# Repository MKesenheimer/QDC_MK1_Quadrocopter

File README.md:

QDC MK1 Quadrocopter
====================

Software für einen Miniatur Quadrocopter (Nanocopter) auf Grundlage der MultiWii-Software. Es wird kein Arduino, sondern ein eigenständiger Flightcontroller (AtXmega32A4) verwendet. Die Software, mit der der Quadrocopter kalibriert werden kann, läuft momentan nur unter Mac OS X.

Um die Software zu kompilieren, müssen die Mac OSX Entwicklertools (XCode) oder GNU g++ installiert sein. Außerdem wird avr-gcc und ein Hardware Programmer (z.B. JTAGICE 3) benötigt.

Kompilieren und Hochladen über PDI der Firmware auf den Quadrocopter:
---------------------------------------------------------------------
- cd firmware
- ./make_Wall oder ./make
- make flash

Erzeugen der GUI QuadroCalibration:
-----------------------------------
- QuadroCalibration.xcodeproj mit XCode öffnen
- kompilieren

Sonstiges:
----------
- der Quadrocopter muss über die serielle Schnittstelle USARTD1 mit dem Computer verbunden werden. Dazu bietet sich ein Arduino an, der standardmäßig ein USB-zu-Seriell-Konverter besitzt. Wichtig: Pegel von 3.3V nicht überschreiten!
- an der seriellen Schnittstelle USARTD0 muss der RC-Empfänger angeschlossen werden (nicht im Schaltplan verzeichnet). In dieser Software Version wird ein DSM2 fähiger Deltang rx31b-K1 verwendet.

Der Quadrocopter lässt sich über eine bestimmte Hebelstellung der Fernsteuerung scharfstellen (Motoren an/aus) und neu initialisieren (Selbstkalibrierung von GYRO und ACCELEROMETER). Siehe dazu main.c 

Bekannte Fehler
---------------
- kein Failsafe implementiert
- keine Spannungsüberwachung
- PID-Werte noch nicht optimal

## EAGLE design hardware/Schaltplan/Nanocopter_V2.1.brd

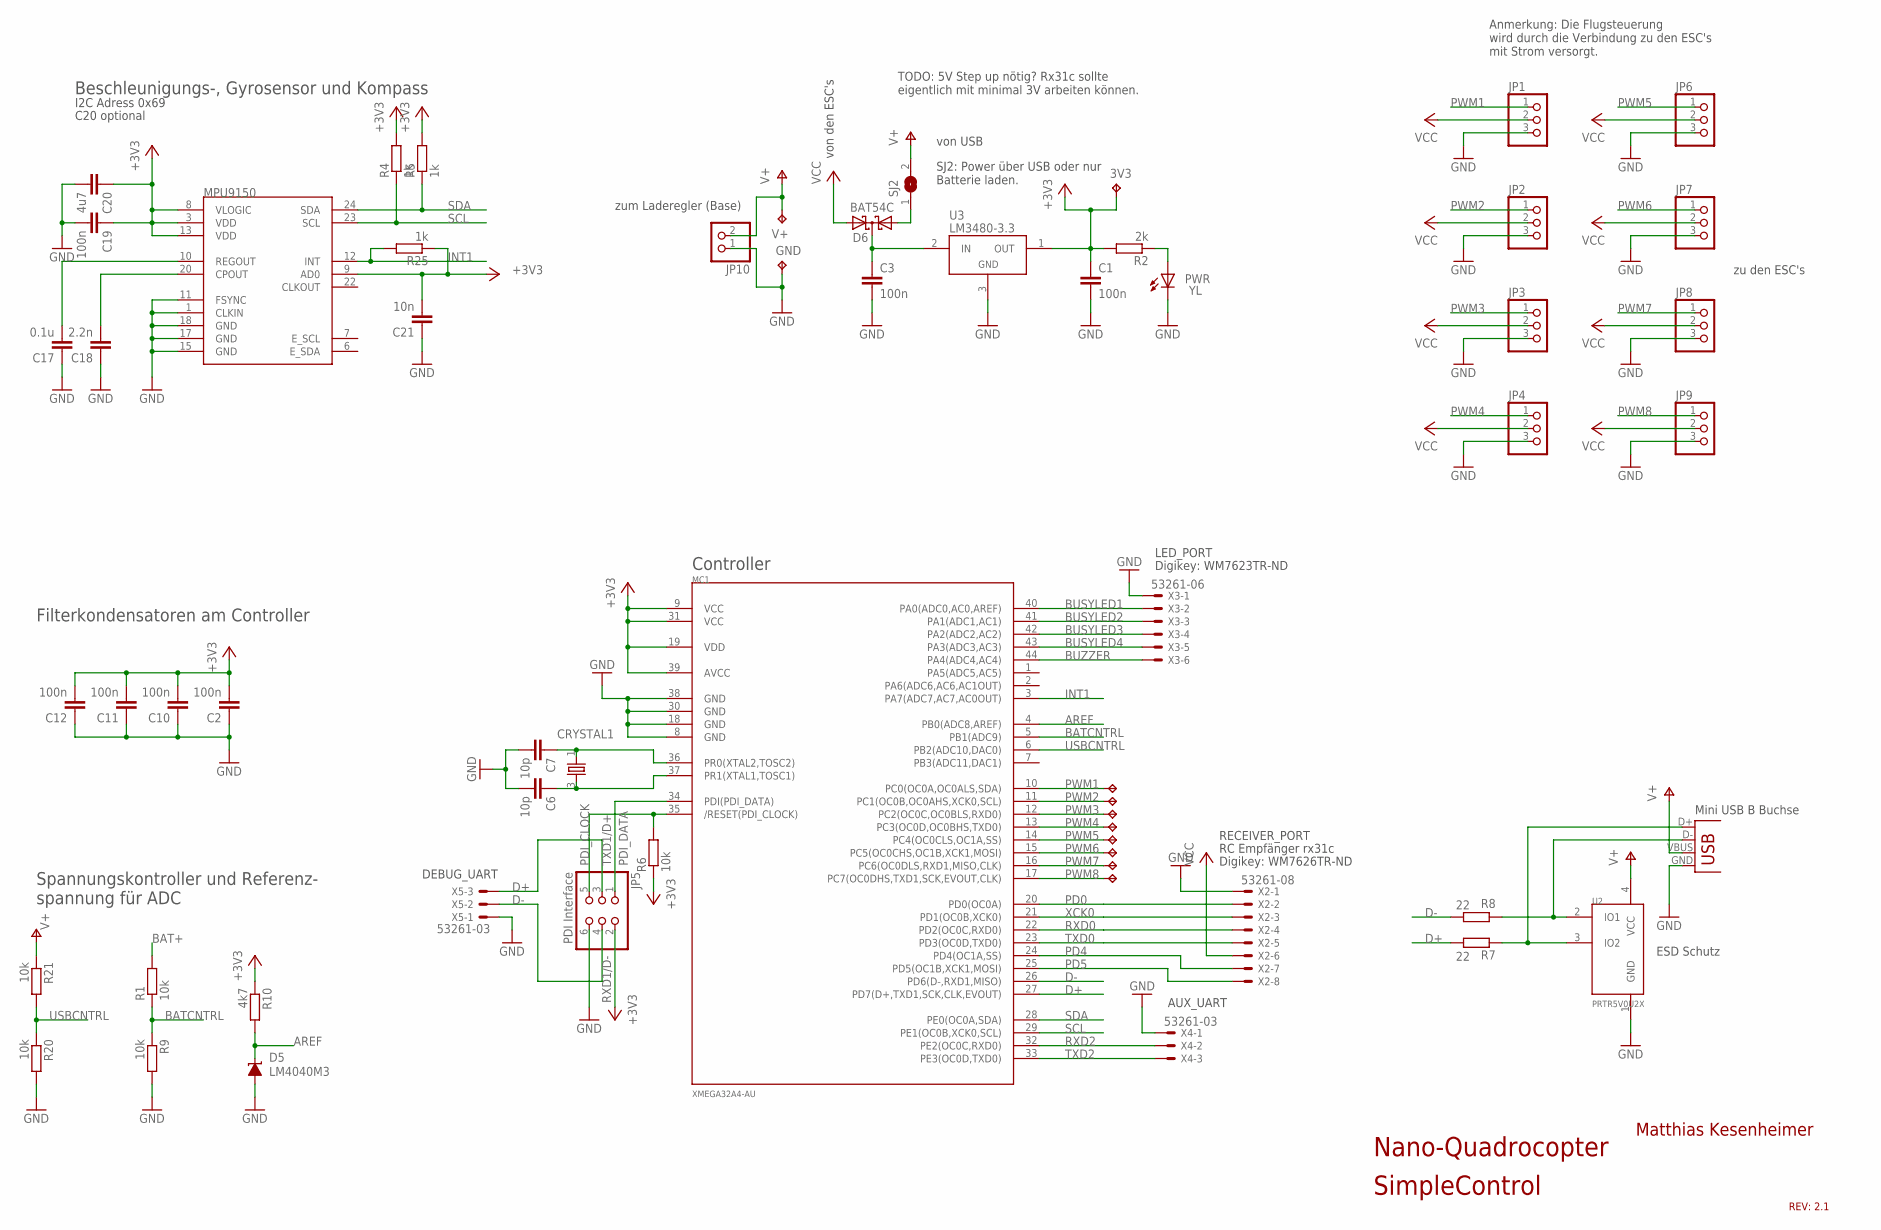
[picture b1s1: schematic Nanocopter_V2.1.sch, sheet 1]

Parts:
3V1, 3V2, 3V3, 3V4, 3V5, 3V6, 3V7, 3V8: TPTP12SQ; TP12SQ
C1, C2, C3, C10, C11, C12, C19: 100n; C0603
C6, C7: 10p; C0603
C17: 0.1u; C0603
C18: 2.2n; C0603
C20: 4u7; C0603
C21: 10n; C0603
CRYSTAL1: CRYSTAL4PIN; CRYSTAL-4PIN
D5: LM4040M3; SOT-23
D6: BAT54C; SOT23
GND: TPTP12SQ; TP12SQ
JP1, JP2, JP3, JP4, JP6, JP7, JP8, JP9: PINHD-1X3; 1X03
JP5: PDI Interface; 2X03
JP10: PINHD-1X2; 1X02
MC1: XMEGA32A4-AU; TQFP44
MPU9150: MPU-9150QFN-24-NP; QFN-24-NP
PWM1: TPTP12SQ; TP12SQ
PWR: YL; CHIPLED_0603
R1, R6, R9, R20, R21: 10k; R0603
R2: 2k; R0603
R4, R5, R25: 1k; R0603
R7, R8: 22; R0603
R10: 4k7; R0603
SJ2: SJ
U2: PRTR5V0U2X; SOT143B
U3: LM3480-3.3; SOT-23-3
V+: TPTP12SQ; TP12SQ
X1: USBSMD; USB-MINIB
X2: 53261-08
X3: 53261-06
X4, X5: 53261-03

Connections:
+3V3: 3V3.TP, C1.1, C2.2, C10.2, C11.2, C12.2, C19.1, C20.1, C21.2, JP5.2, MC1.9 (VCC), MC1.19 (VDD), MC1.31 (VCC), MC1.39 (AVCC), MPU9150.3 (VDD), MPU9150.8 (VLOGIC), MPU9150.9 (AD0), MPU9150.13 (VDD), R2.2, R4.2, R5.2, R6.1, R10.1, R25.1, U3.1 (OUT)
AREF: D5.1 (C), MC1.4 (PB0(ADC8,AREF)), R10.2
BAT+: R1.2
BATCNTRL: MC1.5 (PB1(ADC9)), R1.1, R9.1
BUSYLED1: MC1.40 (PA0(ADC0,AC0,AREF)), X3.2
BUSYLED2: MC1.41 (PA1(ADC1,AC1)), X3.3
BUSYLED3: MC1.42 (PA2(ADC2,AC2)), X3.4
BUSYLED4: MC1.43 (PA3(ADC3,AC3)), X3.5
BUZZER: MC1.44 (PA4(ADC4,AC4)), X3.6
D+: JP5.3, MC1.27 (PD7(D+,TXD1,SCK,CLK,EVOUT)), R7.2, X5.3
D-: JP5.4, MC1.26 (PD6(D-,RXD1,MISO)), R8.2, X5.2
GND: C1.2, C2.1, C3.2, C6.2, C7.2, C10.1, C11.1, C12.1, C17.1, C18.1, C19.2, C20.2, C21.1, D5.2 (A), GND.TP, JP1.3, JP2.3, JP3.3, JP4.3, JP5.6, JP6.3, JP7.3, JP8.3, JP9.3, JP10.1, MC1.8 (GND), MC1.18 (GND), MC1.30 (GND), MC1.38 (GND), MPU9150.1 (CLKIN), MPU9150.11 (FSYNC), MPU9150.15 (GND), MPU9150.17 (GND), MPU9150.18 (GND), PWR.C, R9.2, R20.2, U2.1 (GND), U3.3 (GND), X1.GND, X2.1, X3.1, X4.1, X5.1; also elsewhere on the board
INT1: MC1.3 (PA7(ADC7,AC7,AC0OUT)), MPU9150.12 (INT), R25.2
unnamed: C18.2, MPU9150.20 (CPOUT)
unnamed: C17.2, MPU9150.10 (REGOUT)
unnamed: C3.1, D6.3 (CC), U3.2 (IN)
unnamed: PWR.A, R2.1
unnamed: C7.1, CRYSTAL1.1, MC1.36 (PR0(XTAL2,TOSC2))
unnamed: C6.1, CRYSTAL1.3 (2), MC1.37 (PR1(XTAL1,TOSC1))
unnamed: D6.1 (A1), SJ2.1
PD0: MC1.20 (PD0(OC0A)), X2.2
PD4: MC1.24 (PD4(OC1A,SS)), X2.7
PD5: MC1.25 (PD5(OC1B,XCK1,MOSI)), X2.8
PDI_CLOCK: JP5.5, MC1.35 (/RESET(PDI_CLOCK)), R6.2
PDI_DATA: JP5.1, MC1.34 (PDI(PDI_DATA))
PWM1: JP1.1, MC1.10 (PC0(OC0A,OC0ALS,SDA)), PWM1.TP
PWM2: 3V2.TP, JP2.1, MC1.11 (PC1(OC0B,OC0AHS,XCK0,SCL))
PWM3: 3V4.TP, JP3.1, MC1.12 (PC2(OC0C,OC0BLS,RXD0))
PWM4: 3V5.TP, JP4.1, MC1.13 (PC3(OC0D,OC0BHS,TXD0))
PWM5: 3V1.TP, JP6.1, MC1.14 (PC4(OC0CLS,OC1A,SS))
PWM6: 3V6.TP, JP7.1, MC1.15 (PC5(OC0CHS,OC1B,XCK1,MOSI))
PWM7: 3V7.TP, JP8.1, MC1.16 (PC6(OC0DLS,RXD1,MISO,CLK))
PWM8: 3V8.TP, JP9.1, MC1.17 (PC7(OC0DHS,TXD1,SCK,EVOUT,CLK))
RXD0: MC1.22 (PD2(OC0C,RXD0)), X2.4
RXD2: MC1.32 (PE2(OC0C,RXD0)), X4.2
SCL: MC1.29 (PE1(OC0B,XCK0,SCL)), MPU9150.23 (SCL), R4.1
SDA: MC1.28 (PE0(OC0A,SDA)), MPU9150.24 (SDA), R5.1
TXD0: MC1.23 (PD3(OC0D,TXD0)), X2.5
TXD2: MC1.33 (PE3(OC0D,TXD0)), X4.3
USB+: R7.1, U2.3 (IO2), X1.D+
USB-: R8.1, U2.2 (IO1), X1.D-
USBCNTRL: MC1.6 (PB2(ADC10,DAC0)), R20.1, R21.2
V+: JP10.2, R21.1, SJ2.2, U2.4 (VCC), V+.TP, X1.VBUS
VCC: D6.2 (A2), JP1.2, JP2.2, JP3.2, JP4.2, JP6.2, JP7.2, JP8.2, JP9.2, X2.6; also elsewhere on the board
XCK0: MC1.21 (PD1(OC0B,XCK0)), X2.3

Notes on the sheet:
I2C Adress 0x69
Beschleunigungs-, Gyrosensor und Kompass
Matthias Kesenheimer
REV: 2.1
Nano-Quadrocopter
SimpleControl
Mini USB B Buchse
Controller
Filterkondensatoren am Controller
C20 optional
Spannungskontroller und Referenz- spannung für ADC
ESD Schutz
RC Empfänger rx31c
Digikey: WM7626TR-ND
Digikey: WM7623TR-ND
RXD1/D-
TXD1/D+
DEBUG_UART
AUX_UART
LED_PORT
RECEIVER_PORT
zum Laderegler (Base)
zu den ESC's
Anmerkung: Die Flugsteuerung wird durch die Verbindung zu den ESC's mit Strom versorgt.
von den ESC's
von USB
SJ2: Power über USB oder nur Batterie laden.
TODO: 5V Step up nötig? Rx31c sollte eigentlich mit minimal 3V arbeiten können.

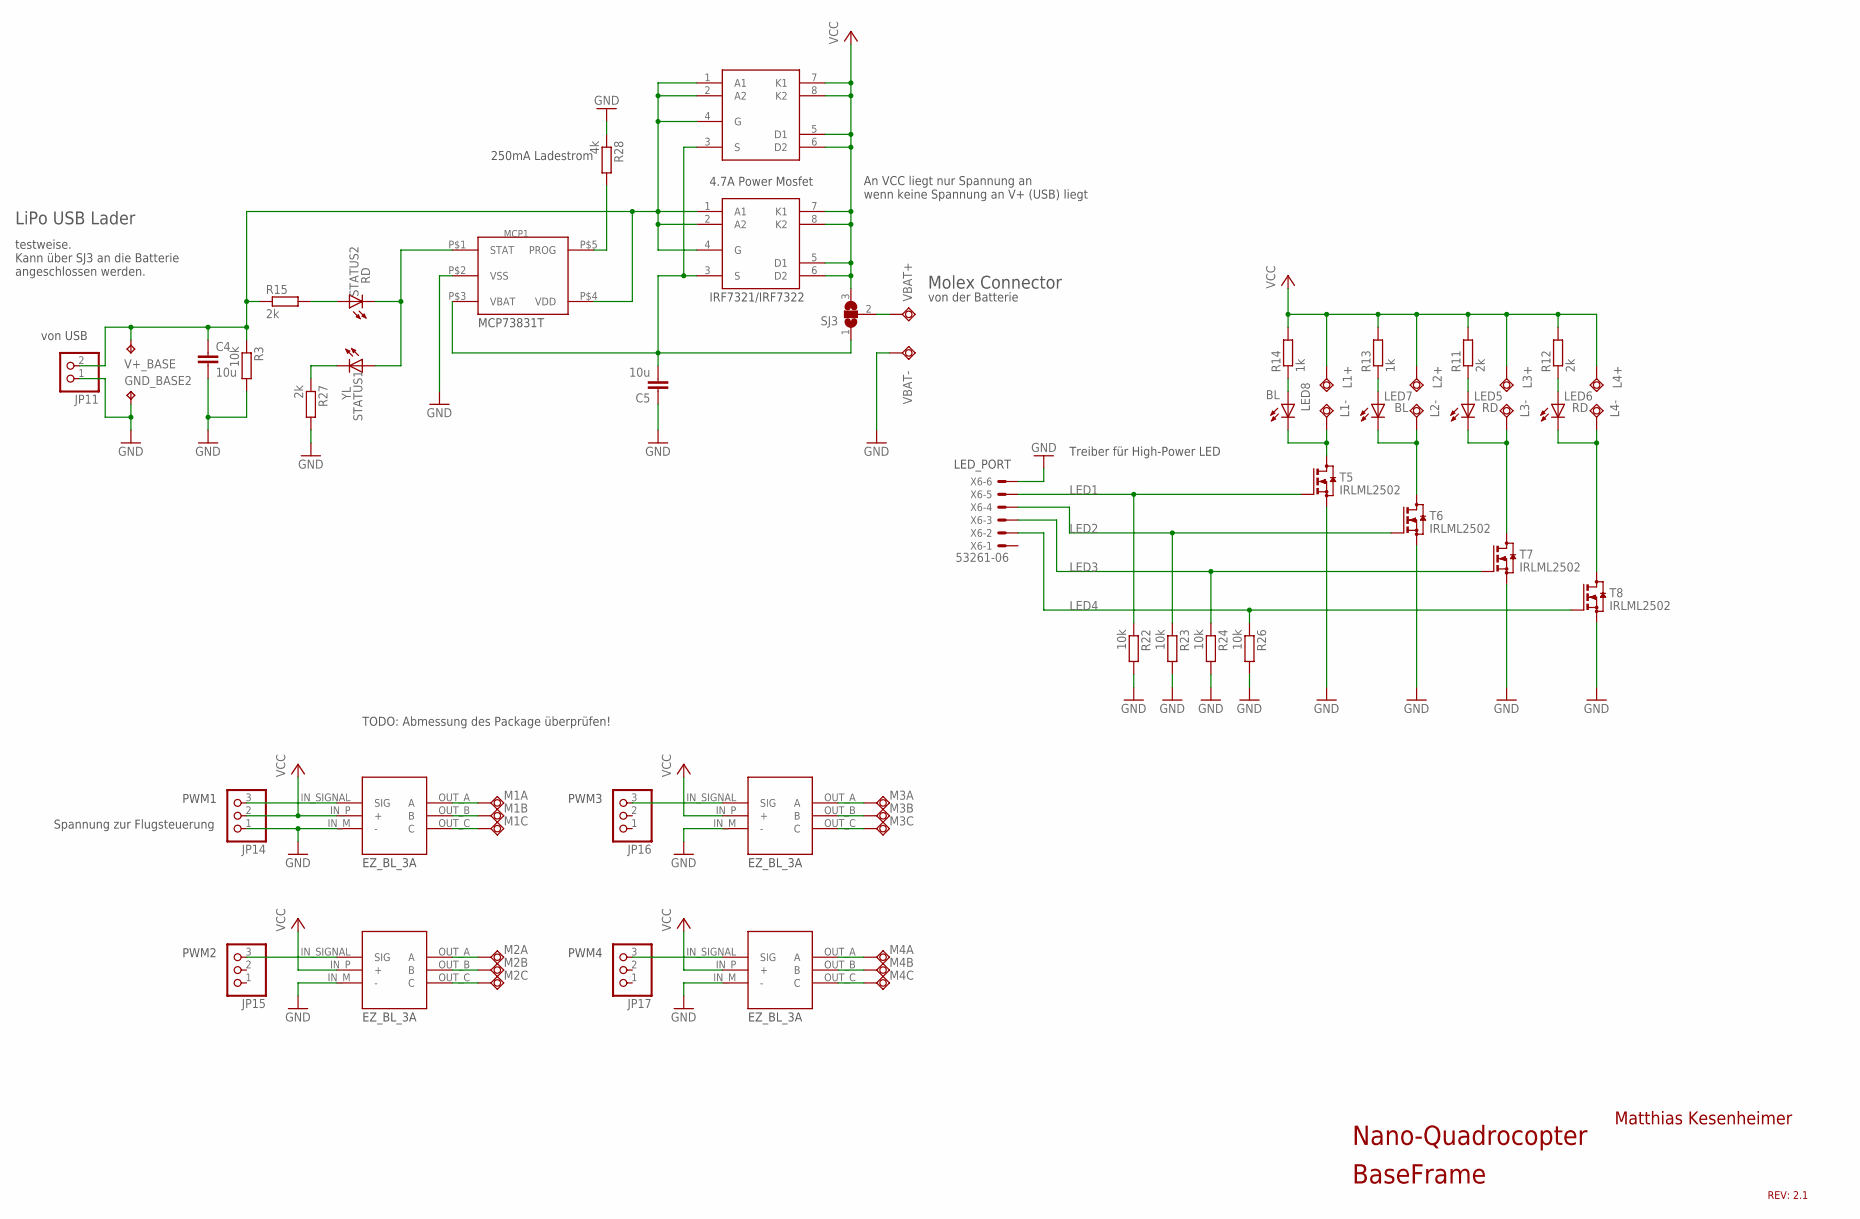
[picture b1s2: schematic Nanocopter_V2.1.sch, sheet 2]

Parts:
C4, C5: 10u; C1206
GND_BASE2: TPTP12SQ; TP12SQ
JP11: PINHD-1X2/90; 1X02/90
JP14, JP15, JP16, JP17: PINHD-1X3/90; 1X03/90
L1+, L1-, L2+, L2-, L3+, L3-, L4+, L4-: TPSQTP20SQ; TP20SQ
LED5, LED6: RD; CHIPLED_0603
LED7, LED8: BL; CHIPLED_0603
M1A, M1B, M1C, M2A, M2B, M2C, M3A, M3B, M3C, M4A, M4B, M4C: TPSQTP20SQ; TP20SQ
MCP1: MCP73831; 5PIN_SOT23
R3, R22, R23, R24, R26: 10k; R0603
R11, R12, R15, R27: 2k; R0603
R13, R14: 1k; R0603
R28: 4k; R0603
SJ3: SJ2W; SJ_2
STATUS1: YL; CHIPLED_0603
STATUS2: RD; CHIPLED_0603
T5, T6, T7, T8: IRLML2502; SOT23
U$1, U$2, U$3, U$4: EAZY_BL_3A; EZ_BL_3A_P
U$5, U$6: IRF7321; SO8
V+_BASE: TPTP12SQ; TP12SQ
VBAT+: TPSQTP20SQ; TP20SQ
VBAT-: TPSQTP20SQ; TP20SQ
X6: 53261-06

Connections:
GND: C4.2, C5.1, GND_BASE2.TP, JP11.1, JP14.1, MCP1.P$2 (VSS), R3.2, R22.2, R23.2, R24.2, R26.2, R27.2, R28.1, T5.2 (S), T6.2 (S), T7.2 (S), T8.2 (S), U$1.IN_M (-), U$2.IN_M (-), U$3.IN_M (-), U$4.IN_M (-), VBAT-.TP, X6.6; also elsewhere on the board
LED1: R22.1, T5.1 (G), X6.5
LED2: R23.1, T6.1 (G), X6.4
LED3: R24.1, T7.1 (G), X6.3
LED4: R26.1, T8.1 (G), X6.2
unnamed: LED5.A, R11.1
unnamed: LED6.A, R12.1
unnamed: LED7.A, R13.1
unnamed: L1-.TP, LED8.C, T5.3 (D)
unnamed: L3-.TP, LED5.C, T7.3 (D)
unnamed: L4-.TP, LED6.C, T8.3 (D)
unnamed: L2-.TP, LED7.C, T6.3 (D)
unnamed: MCP1.P$5 (PROG), R28.2
unnamed: JP14.3, U$1.IN_SIGNAL (SIG)
unnamed: M2A.TP, U$2.OUT_A (A)
unnamed: LED8.A, R14.1
unnamed: C5.2, MCP1.P$3 (VBAT), SJ3.1, U$5.3 (S), U$6.3 (S)
unnamed: M2B.TP, U$2.OUT_B (B)
unnamed: M2C.TP, U$2.OUT_C (C)
unnamed: R15.2, STATUS2.A
unnamed: M1A.TP, U$1.OUT_A (A)
unnamed: M1B.TP, U$1.OUT_B (B)
unnamed: M1C.TP, U$1.OUT_C (C)
unnamed: JP15.3, U$2.IN_SIGNAL (SIG)
unnamed: M3A.TP, U$3.OUT_A (A)
unnamed: M3B.TP, U$3.OUT_B (B)
unnamed: M3C.TP, U$3.OUT_C (C)
unnamed: JP16.3, U$3.IN_SIGNAL (SIG)
unnamed: M4A.TP, U$4.OUT_A (A)
unnamed: M4B.TP, U$4.OUT_B (B)
unnamed: M4C.TP, U$4.OUT_C (C)
unnamed: JP17.3, U$4.IN_SIGNAL (SIG)
unnamed: R27.1, STATUS1.C
unnamed: MCP1.P$1 (STAT), STATUS1.A, STATUS2.C
unnamed: SJ3.2, VBAT+.TP
VCC: JP14.2, L1+.TP, L2+.TP, L3+.TP, L4+.TP, R11.2, R12.2, R13.2, R14.2, SJ3.3, U$1.IN_P (+), U$2.IN_P (+), U$3.IN_P (+), U$4.IN_P (+), U$5.5 (D1), U$5.6 (D2), U$5.7 (K1), U$5.8 (K2), U$6.5 (D1), U$6.6 (D2), U$6.7 (K1), U$6.8 (K2); also elsewhere on the board
VDD: C4.1, JP11.2, MCP1.P$4 (VDD), R3.1, R15.1, U$5.1 (A1), U$5.2 (A2), U$5.4 (G), U$6.1 (A1), U$6.2 (A2), U$6.4 (G), V+_BASE.TP

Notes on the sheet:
LiPo USB Lader
250mA Ladestrom
Matthias Kesenheimer
REV: 2.1
Nano-Quadrocopter
BaseFrame
Treiber für High-Power LED
Molex Connector
PWM1
PWM2
PWM3
PWM4
Spannung zur Flugsteuerung
von der Batterie
von USB
LED_PORT
testweise. Kann über SJ3 an die Batterie angeschlossen werden.
4.7A Power Mosfet
IRF7321/IRF7322
MCP73831T
An VCC liegt nur Spannung an wenn keine Spannung an V+ (USB) liegt
TODO: Abmessung des Package überprüfen!
EZ_BL_3A

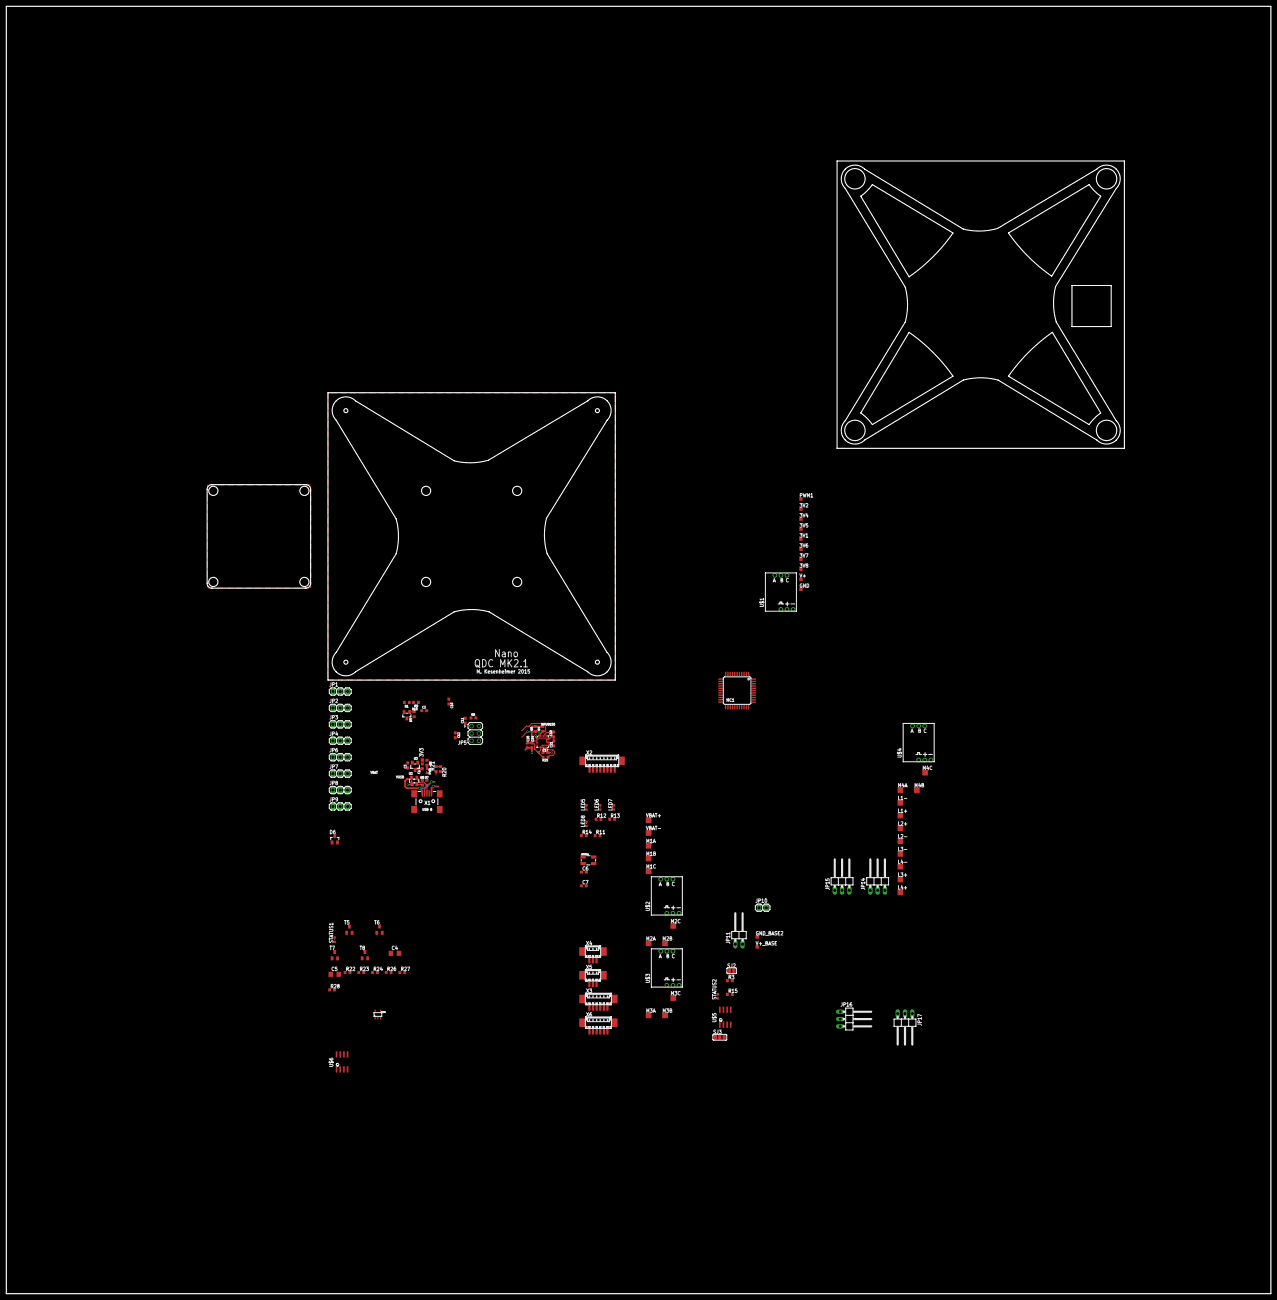
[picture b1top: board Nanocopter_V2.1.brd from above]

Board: 2 copper layers, 440.1 x 448.0 mm, 122 parts (0 on the bottom side), 79 nets.

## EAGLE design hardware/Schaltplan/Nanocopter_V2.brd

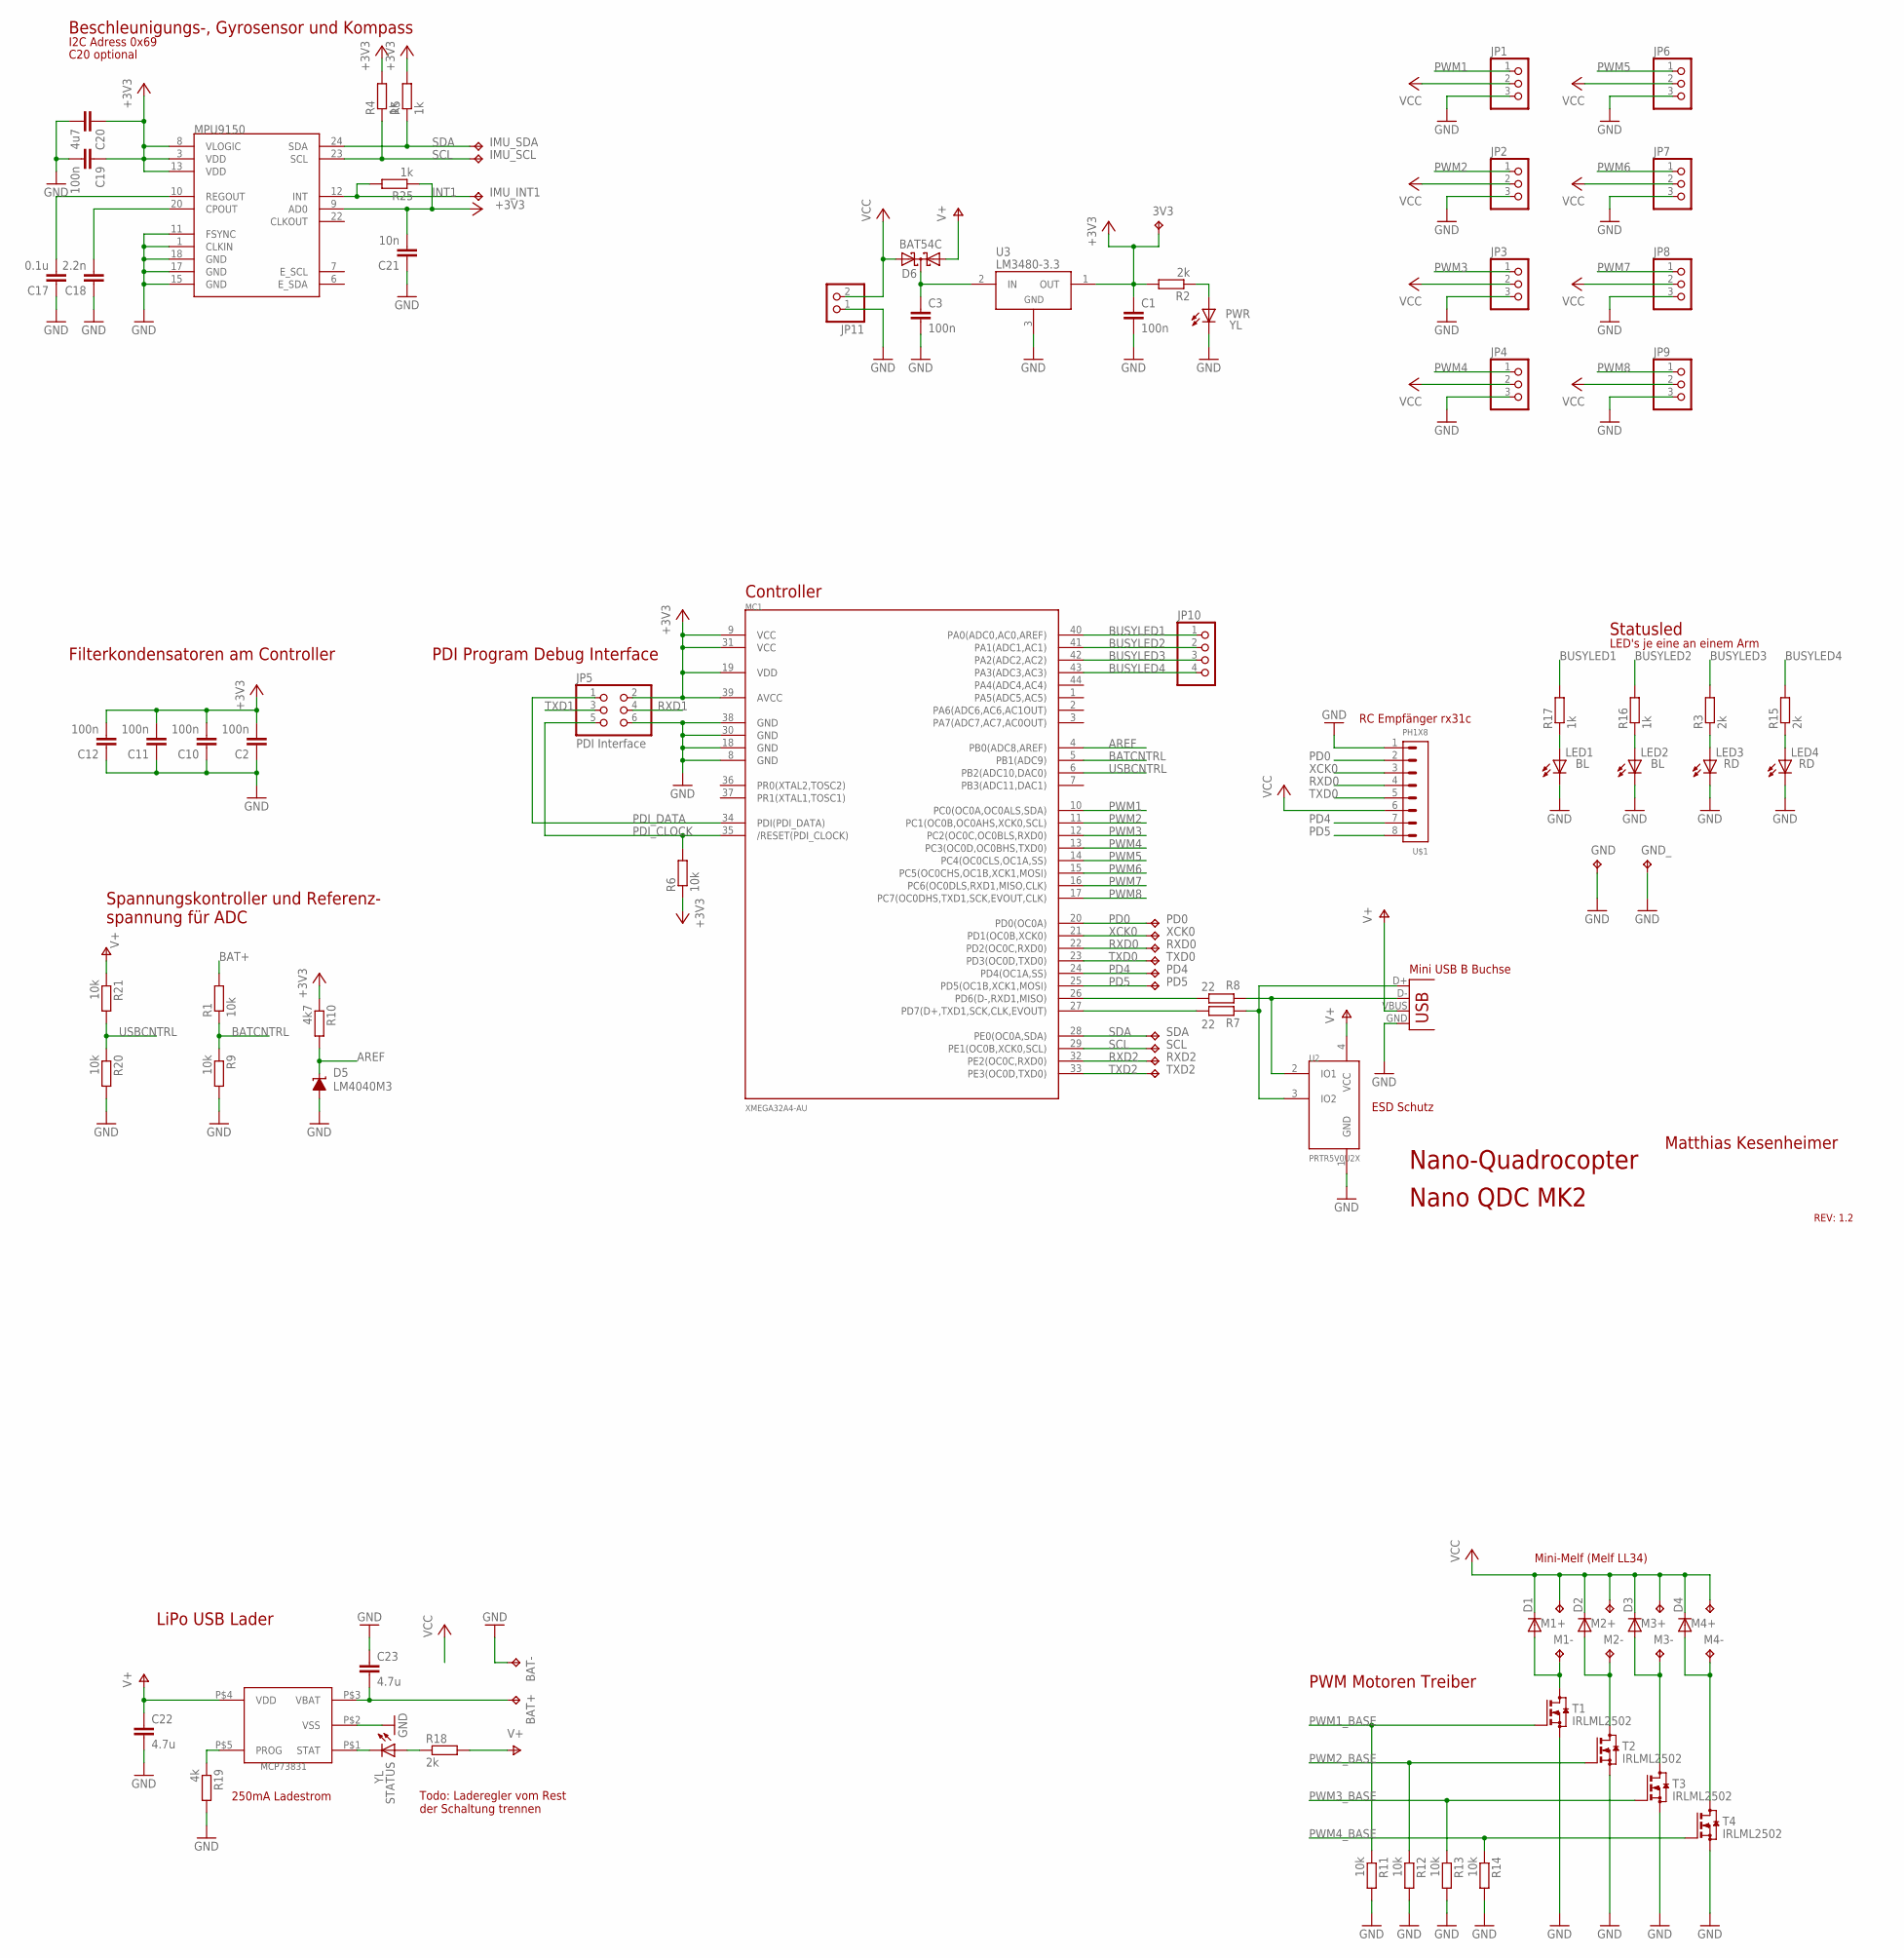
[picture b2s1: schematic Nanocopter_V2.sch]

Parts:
3V3: TPTP12SQ; TP12SQ
BAT+: TPTP12SQ; TP12SQ
BAT-: TPTP12SQ; TP12SQ
C1, C2, C3, C10, C11, C12, C19: 100n; C0603
C17: 0.1u; C0603
C18: 2.2n; C0603
C20: 4u7; C0603
C21: 10n; C0603
C22, C23: 4.7u; C1206
D1, D2, D3, D4: DIODE-MINIMELF; MINIMELF
D5: LM4040M3; SOT-23
D6: BAT54C; SOT23
GND: TPTP12SQ; TP12SQ
GND_: TPTP12SQ; TP12SQ
IMU_INT1: TPTP10SQ; TP10SQ
IMU_SCL: TPTP10SQ; TP10SQ
IMU_SDA: TPTP10SQ; TP10SQ
JP1, JP2, JP3, JP4, JP6, JP7, JP8, JP9: PINHD-1X3; 1X03
JP5: PDI Interface; 2X03
JP10: PINHD-1X4; 1X04
JP11: PINHD-1X2; 1X02
LED1, LED2: BL; CHIPLED_0603
LED3, LED4: RD; CHIPLED_0603
M1+, M1-, M2+, M2-, M3+, M3-, M4+, M4-: TPTP15SQ; TP15SQ
MC1: XMEGA32A4-AU; TQFP44
MCP73831: MCP73831; 5PIN_SOT23
MPU9150: MPU-9150QFN-24-NP; QFN-24-NP
PD0, PD4, PD5: TPTP10SQ; TP10SQ
PWR: YL; CHIPLED_0603
R1, R6, R9, R11, R12, R13, R14, R20, R21: 10k; R0603
R2, R3, R15, R18: 2k; R0603
R4, R5, R16, R17, R25: 1k; R0603
R7, R8: 22; R0603
R10: 4k7; R0603
R19: 4k; R0603
RXD0, RXD2: TPTP10SQ; TP10SQ
SCL: TPTP10SQ; TP10SQ
SDA: TPTP10SQ; TP10SQ
STATUS: YL; CHIPLED_0603
T1, T2, T3, T4: IRLML2502; SOT23
TXD0, TXD2: TPTP10SQ; TP10SQ
U2: PRTR5V0U2X; SOT143B
U3: LM3480-3.3; SOT-23-3
U$1: PH1X8; PHL005-1-8
X1: USBSMD; USB-MINIB
XCK0: TPTP10SQ; TP10SQ

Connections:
+3V3: 3V3.TP, C1.1, C2.2, C10.2, C11.2, C12.2, C19.1, C20.1, C21.2, JP5.2, MC1.9 (VCC), MC1.19 (VDD), MC1.31 (VCC), MC1.39 (AVCC), MPU9150.3 (VDD), MPU9150.8 (VLOGIC), MPU9150.9 (AD0), MPU9150.13 (VDD), R2.2, R4.2, R5.2, R6.1, R10.1, R25.1, U3.1 (OUT)
AREF: D5.1 (C), MC1.4 (PB0(ADC8,AREF)), R10.2
BAT+: BAT+.TP, C23.2, MCP73831.P$3 (VBAT), R1.2
BATCNTRL: MC1.5 (PB1(ADC9)), R1.1, R9.1
BUSYLED1: JP10.1, MC1.40 (PA0(ADC0,AC0,AREF)), R17.2
BUSYLED2: JP10.2, MC1.41 (PA1(ADC1,AC1)), R16.2
BUSYLED3: JP10.3, MC1.42 (PA2(ADC2,AC2)), R3.2
BUSYLED4: JP10.4, MC1.43 (PA3(ADC3,AC3)), R15.2
GND: BAT-.TP, C1.2, C2.1, C3.2, C10.1, C11.1, C12.1, C17.1, C18.1, C19.2, C20.2, C21.1, C22.2, C23.1, D5.2 (A), GND.TP, GND_.TP, JP1.3, JP2.3, JP3.3, JP4.3, JP5.6, JP6.3, JP7.3, JP8.3, JP9.3, JP11.1, LED1.C, LED2.C, LED3.C, LED4.C, MC1.8 (GND), MC1.18 (GND), MC1.30 (GND), MC1.38 (GND), MCP73831.P$2 (VSS), MPU9150.1 (CLKIN), MPU9150.11 (FSYNC), MPU9150.15 (GND), MPU9150.17 (GND), MPU9150.18 (GND), PWR.C, R9.2, R11.2, R12.2, R13.2, R14.2, R19.2, R20.2, T1.2 (S), T2.2 (S), T3.2 (S), T4.2 (S), U2.1 (GND), U3.3 (GND), U$1.1, X1.GND
INT1: IMU_INT1.TP, MPU9150.12 (INT), R25.2
unnamed: C18.2, MPU9150.20 (CPOUT)
unnamed: MCP73831.P$1 (STAT), STATUS.C
unnamed: R18.1, STATUS.A
unnamed: MCP73831.P$5 (PROG), R19.1
unnamed: C17.2, MPU9150.10 (REGOUT)
unnamed: C3.1, D6.3 (CC), U3.2 (IN)
unnamed: PWR.A, R2.1
unnamed: LED3.A, R3.1
unnamed: LED4.A, R15.1
unnamed: LED2.A, R16.1
unnamed: LED1.A, R17.1
unnamed: D1.A, M1-.TP, T1.3 (D)
unnamed: D3.A, M3-.TP, T3.3 (D)
unnamed: D4.A, M4-.TP, T4.3 (D)
unnamed: D2.A, M2-.TP, T2.3 (D)
PD0: MC1.20 (PD0(OC0A)), PD0.TP, U$1.2
PD4: MC1.24 (PD4(OC1A,SS)), PD4.TP, U$1.7
PD5: MC1.25 (PD5(OC1B,XCK1,MOSI)), PD5.TP, U$1.8
PDI_CLOCK: JP5.5, MC1.35 (/RESET(PDI_CLOCK)), R6.2
PDI_DATA: JP5.1, MC1.34 (PDI(PDI_DATA))
PWM1: JP1.1, MC1.10 (PC0(OC0A,OC0ALS,SDA))
PWM1_BASE: R11.1, T1.1 (G)
PWM2: JP2.1, MC1.11 (PC1(OC0B,OC0AHS,XCK0,SCL))
PWM2_BASE: R12.1, T2.1 (G)
PWM3: JP3.1, MC1.12 (PC2(OC0C,OC0BLS,RXD0))
PWM3_BASE: R13.1, T3.1 (G)
PWM4: JP4.1, MC1.13 (PC3(OC0D,OC0BHS,TXD0))
PWM4_BASE: R14.1, T4.1 (G)
PWM5: JP6.1, MC1.14 (PC4(OC0CLS,OC1A,SS))
PWM6: JP7.1, MC1.15 (PC5(OC0CHS,OC1B,XCK1,MOSI))
PWM7: JP8.1, MC1.16 (PC6(OC0DLS,RXD1,MISO,CLK))
PWM8: JP9.1, MC1.17 (PC7(OC0DHS,TXD1,SCK,EVOUT,CLK))
RXD0: MC1.22 (PD2(OC0C,RXD0)), RXD0.TP, U$1.4
RXD1: JP5.4, MC1.26 (PD6(D-,RXD1,MISO)), R8.2
RXD2: MC1.32 (PE2(OC0C,RXD0)), RXD2.TP
SCL: IMU_SCL.TP, MC1.29 (PE1(OC0B,XCK0,SCL)), MPU9150.23 (SCL), R4.1, SCL.TP
SDA: IMU_SDA.TP, MC1.28 (PE0(OC0A,SDA)), MPU9150.24 (SDA), R5.1, SDA.TP
TXD0: MC1.23 (PD3(OC0D,TXD0)), TXD0.TP, U$1.5
TXD1: JP5.3, MC1.27 (PD7(D+,TXD1,SCK,CLK,EVOUT)), R7.2
TXD2: MC1.33 (PE3(OC0D,TXD0)), TXD2.TP
USB+: R7.1, U2.3 (IO2), X1.D+
USB-: R8.1, U2.2 (IO1), X1.D-
USBCNTRL: MC1.6 (PB2(ADC10,DAC0)), R20.1, R21.2
V+: D6.1 (A1), R18.2, R21.1, U2.4 (VCC), X1.VBUS
VCC: D1.C, D2.C, D3.C, D4.C, D6.2 (A2), JP1.2, JP2.2, JP3.2, JP4.2, JP6.2, JP7.2, JP8.2, JP9.2, JP11.2, M1+.TP, M2+.TP, M3+.TP, M4+.TP, U$1.6
VDD: C22.1, MCP73831.P$4 (VDD)
XCK0: MC1.21 (PD1(OC0B,XCK0)), U$1.3, XCK0.TP

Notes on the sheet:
I2C Adress 0x69
Beschleunigungs-, Gyrosensor und Kompass
PWM Motoren Treiber
Statusled
PDI Program Debug Interface
Matthias Kesenheimer
REV: 1.2
Nano-Quadrocopter
Nano QDC MK2
Mini USB B Buchse
Controller
Filterkondensatoren am Controller
C20 optional
Spannungskontroller und Referenz- spannung für ADC
LED's je eine an einem Arm
ESD Schutz
RC Empfänger rx31c
Mini-Melf (Melf LL34)
LiPo USB Lader
250mA Ladestrom
Todo: Laderegler vom Rest der Schaltung trennen

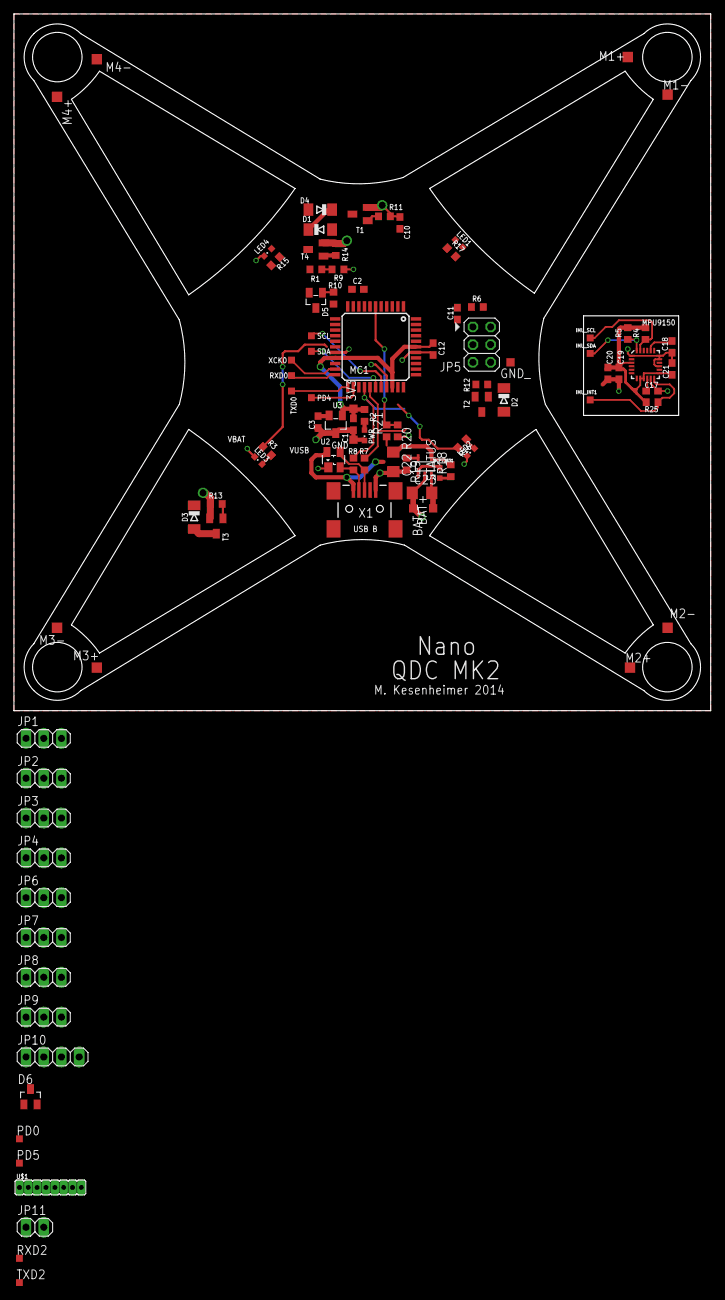
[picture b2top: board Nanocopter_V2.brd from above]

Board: 2 copper layers, 100.0 x 100.0 mm, 95 parts (0 on the bottom side), 57 nets.

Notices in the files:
parts and their libraries:
SparkFun-Sensors: Licensing: Creative Commons ShareAlike 4.0 International - https://creativecommons.org/licenses/by-sa/4.0
SparkFun: Released under the Creative Commons Attribution Share-Alike 3.0 License
SparkFun: http://creativecommons.org/licenses/by-sa/3.0
